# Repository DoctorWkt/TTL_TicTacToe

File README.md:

# TTL_TicTacToe

I've seen several circuits for two-player tic-tac-toe games on the Internet,
but I thought I'd try to design one with these constraints:

 + done with TTL components only, no CPU
 + minimum number of chips
 + not two player: human versus the board, board makes optimal moves

This is the repository for my result. The circuit uses flip-flops to
register both the human and the board's moves. The board has a register
which holds the current state of the board's moves. The board state and
the user's moves are combined to access a ROM to look up the next board move
and any tie or win result.
An [overview of the design](design_notes.md) is available. Here's
a [video](https://www.youtube.com/watch?v=WPPjL46z-Ag) of the board in action.

There are several versions of the design.

## Logisim Version

I built this [Logisim version](ttt_wkt.circ) in preparation for
designing the real circuit with TTL components. If you haven't used
[Logisim](http://www.cburch.com/logisim/) before, open up the _*.circ_
file. Now start the clock with a control-K (or use
_Simulate -> Ticks Enabled_). Now that the circuit is running, click on
the brown finger icon (the poke tool) at the top-left so that you can
press the game buttons.

Over on the right you will see a 3x3 grid. The white squares are the
pushbuttons to make a move. Next to each button is a red LED to register
the user's move and a blue LED for the board's moves.

Below this grid there is a Reset button and a "Who Goes First" button.
Press the "Who Goes First" button to toggle between the user moving
first and the board moving first. Then press the Reset button to clear
the board.

Now press the user moves buttons to make your moves. Immediately after
each move, the board will make a move. When a tie occurs, the Tie LED
will light up. When the board wins, the Win LED will light up.

Over on the left are the nine JK flip-flops to record the user's moves,
and the nine JK flip-flops to record the board's moves. Below that is
the ROM which generates a 4-bit value which is the new board's move.
The 4-bit board move goes into the 4:16 demultiplexer to generate the nine
lines which go to the nine JK flip-flops to record the board's moves.
Two of the 16 possible moves are used to indicate a tie or a board win.

The ROM also generates the next state of the board's moves. This is
recorded into a 4-bit register. See the [design notes](design_notes.md)
for details of the state number.

The circuit should come with the latest version of the ROM image. If you
ever regenerate the _ttt.rom_ file, here is how to load it into the circuit.
Right-click on the ROM device in the circuit and choose *Load image* and
choose the _ttl.rom_ file to load.

## Kicad Schematic

In the _Schematic/_ folder you will find a
[Kicad schematic](Schematic/schematic.pdf) for the circuit. This uses:

 + nine 74HC107 dual JK flip flops. Each one holds both the user and board
   move for one position on the board
 + one 28C256 32Kx8 EEPROM to look up the next board move. We only use
   8K of the space in the EEPROM.
 + one 74HC154 4:16 demultiplexer
 + one 75HC161 register to hold the board state number
 + one 555 to generate the clock signal
 + various LEDs to show the moves, and other sundry components.

I've also designed a [PCB](Figs/pcb2.jpg) to hold all the components.
The design has separate LEDs for user and board moves, but I've chosen to use
bi-colour LEDs so that there is a single physical LED for each board position:
green for the user, red for the board, off when empty.

## Generating the 28C256 EEPROM Contents

At the Linux command-line, run the command:

```
make
```

This will use the _gen_moves.pl_ script to generate the user-first moves file
_umoves_, and the board-first moves file _bmoves_. These are then parsed by
the _parse_moves.pl_ script to create the _ttt.rom_ file used by Logisim.

Finally, the _hex2bin_ script takes the _ttt.rom_ file, which is hex-encoded,
and converts it to the binary file _28C256.bin_ which can be burned to the
EEPROM.

If you have a MiniPro EEPROM burner and the _minipro_ command installed,

```
make write
```

will burn the _28C256.bin_ to a 28C256 chip with the MiniPro burner.

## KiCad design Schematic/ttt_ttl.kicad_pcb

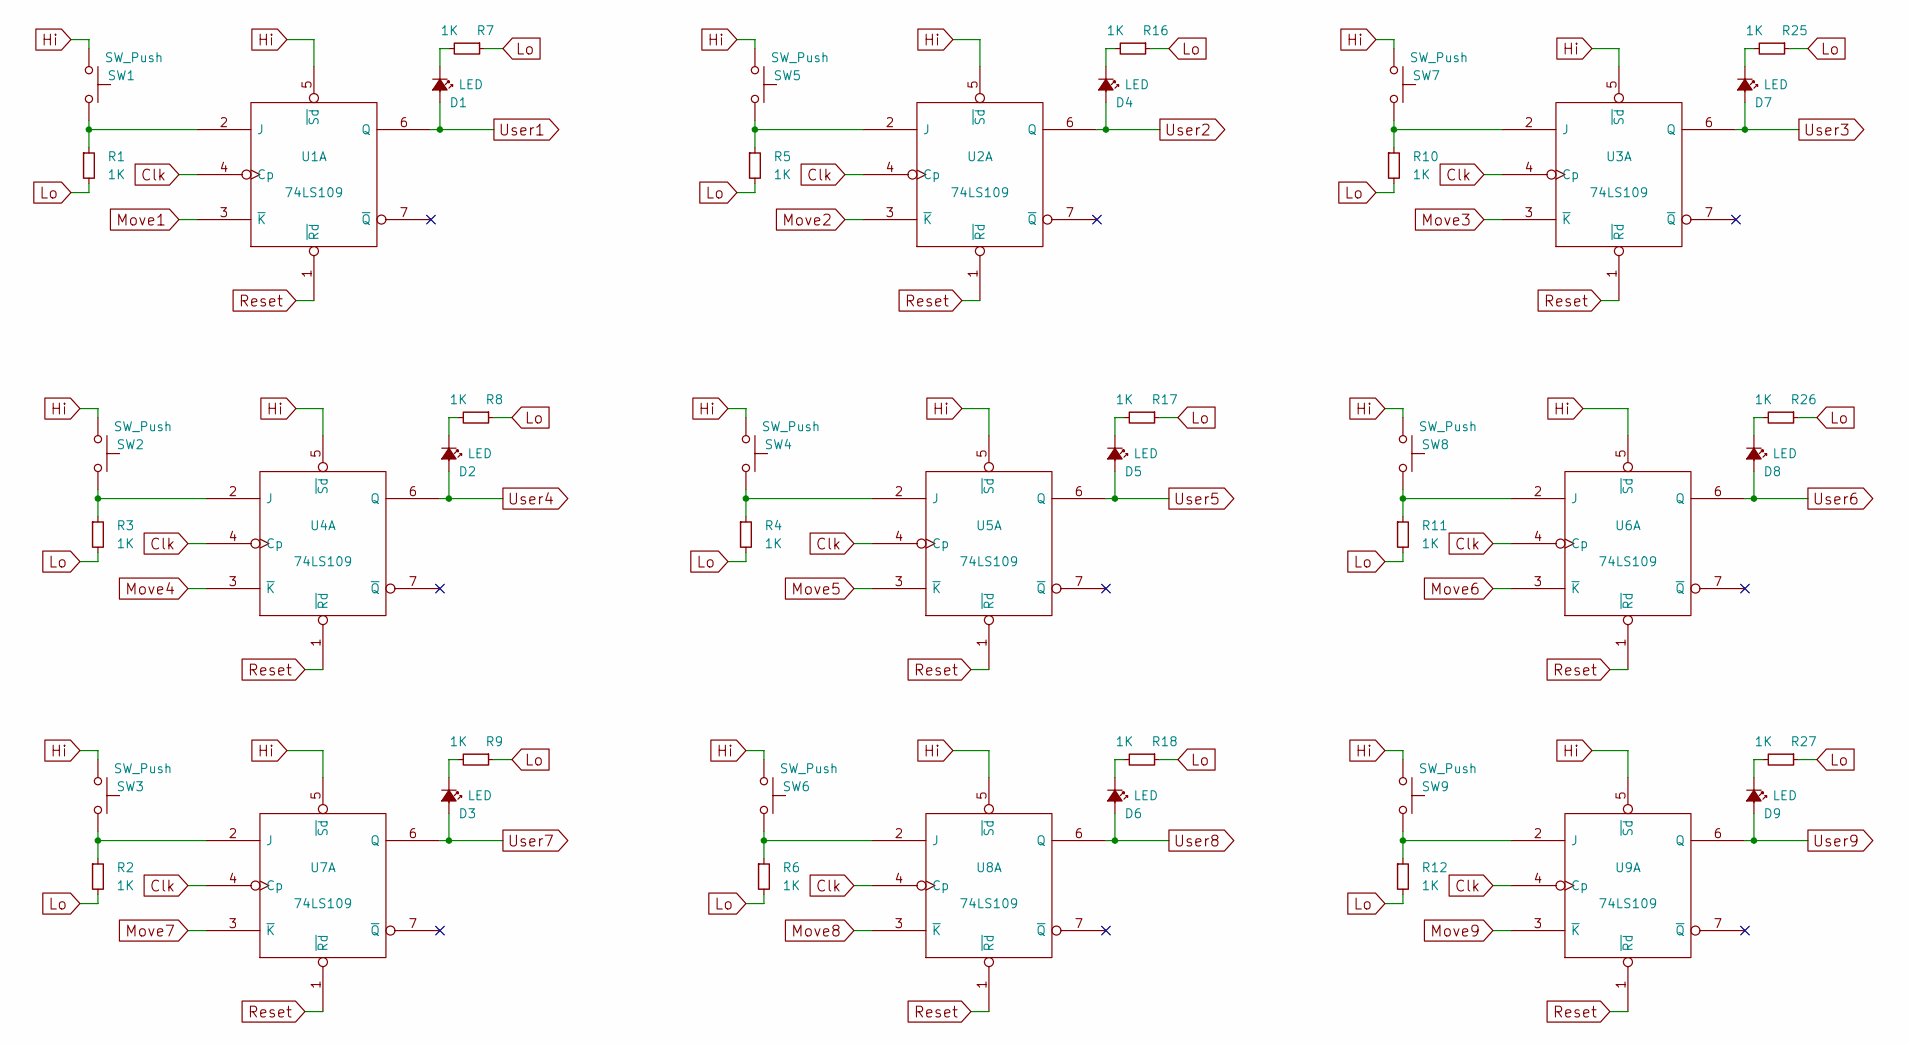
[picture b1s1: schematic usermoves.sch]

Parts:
D1, D2, D3, D4, D5, D6, D7, D8, D9: LED; LED_D3.0mm
R1, R2, R3, R4, R5, R6, R7, R8, R9, R10, R11, R12, R16, R17, R18, R25, R26, R27: 1K; R_Axial_DIN0207_L6.3mm_D2.5mm_P7.62mm_Horizontal
SW1, SW2, SW3, SW4, SW5, SW6, SW7, SW8, SW9: SW_Push; Push_E-Switch_KS01Q01
U1, U2, U3, U4, U5, U6, U7, U8, U9: 74LS109; DIP-16_W7.62mm

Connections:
Clk: U1.4 (Cp), U2.4 (Cp), U3.4 (Cp), U4.4 (Cp), U5.4 (Cp), U6.4 (Cp), U7.4 (Cp), U8.4 (Cp), U9.4 (Cp); also elsewhere on the board
Hi: SW1.1, SW2.1, SW3.1, SW4.1, SW5.1, SW6.1, SW7.1, SW8.1, SW9.1, U1.5 (~Sd), U1.16 (VCC), U2.5 (~Sd), U2.16 (VCC), U3.5 (~Sd), U3.16 (VCC), U4.5 (~Sd), U4.16 (VCC), U5.5 (~Sd), U5.16 (VCC), U6.5 (~Sd), U6.16 (VCC), U7.5 (~Sd), U7.16 (VCC), U8.5 (~Sd), U8.16 (VCC), U9.5 (~Sd), U9.16 (VCC); also elsewhere on the board
Lo: R1.2, R2.2, R3.2, R4.2, R5.2, R6.2, R7.1, R8.1, R9.1, R10.2, R11.2, R12.2, R16.1, R17.1, R18.1, R25.1, R26.1, R27.1, U1.8 (GND), U2.8 (GND), U3.8 (GND), U4.8 (GND), U5.8 (GND), U6.8 (GND), U7.8 (GND), U8.8 (GND), U9.8 (GND); also elsewhere on the board
Move1: U1.3 (~K); also elsewhere on the board
Move2: U2.3 (~K); also elsewhere on the board
Move3: U3.3 (~K); also elsewhere on the board
Move4: U4.3 (~K); also elsewhere on the board
Move5: U5.3 (~K); also elsewhere on the board
Move6: U6.3 (~K); also elsewhere on the board
Move7: U7.3 (~K); also elsewhere on the board
Move8: U8.3 (~K); also elsewhere on the board
Move9: U9.3 (~K); also elsewhere on the board
unnamed: D1.1 (K), R7.2
unnamed: D2.1 (K), R8.2
unnamed: D3.1 (K), R9.2
unnamed: D4.1 (K), R16.2
unnamed: D5.1 (K), R17.2
unnamed: D6.1 (K), R18.2
unnamed: D7.1 (K), R25.2
unnamed: D8.1 (K), R26.2
unnamed: D9.1 (K), R27.2
unnamed: R1.1, SW1.2, U1.2 (J)
unnamed: R2.1, SW3.2, U7.2 (J)
unnamed: R3.1, SW2.2, U4.2 (J)
unnamed: R4.1, SW4.2, U5.2 (J)
unnamed: R5.1, SW5.2, U2.2 (J)
unnamed: R6.1, SW6.2, U8.2 (J)
unnamed: R10.1, SW7.2, U3.2 (J)
unnamed: R11.1, SW8.2, U6.2 (J)
unnamed: R12.1, SW9.2, U9.2 (J)
Reset: U1.1 (~Rd), U2.1 (~Rd), U3.1 (~Rd), U4.1 (~Rd), U5.1 (~Rd), U6.1 (~Rd), U7.1 (~Rd), U8.1 (~Rd), U9.1 (~Rd); also elsewhere on the board
User1: D1.2 (A), U1.6 (Q); also elsewhere on the board
User2: D4.2 (A), U2.6 (Q); also elsewhere on the board
User3: D7.2 (A), U3.6 (Q); also elsewhere on the board
User4: D2.2 (A), U4.6 (Q); also elsewhere on the board
User5: D5.2 (A), U5.6 (Q); also elsewhere on the board
User6: D8.2 (A), U6.6 (Q); also elsewhere on the board
User7: D3.2 (A), U7.6 (Q); also elsewhere on the board
User8: D6.2 (A), U8.6 (Q); also elsewhere on the board
User9: D9.2 (A), U9.6 (Q); also elsewhere on the board

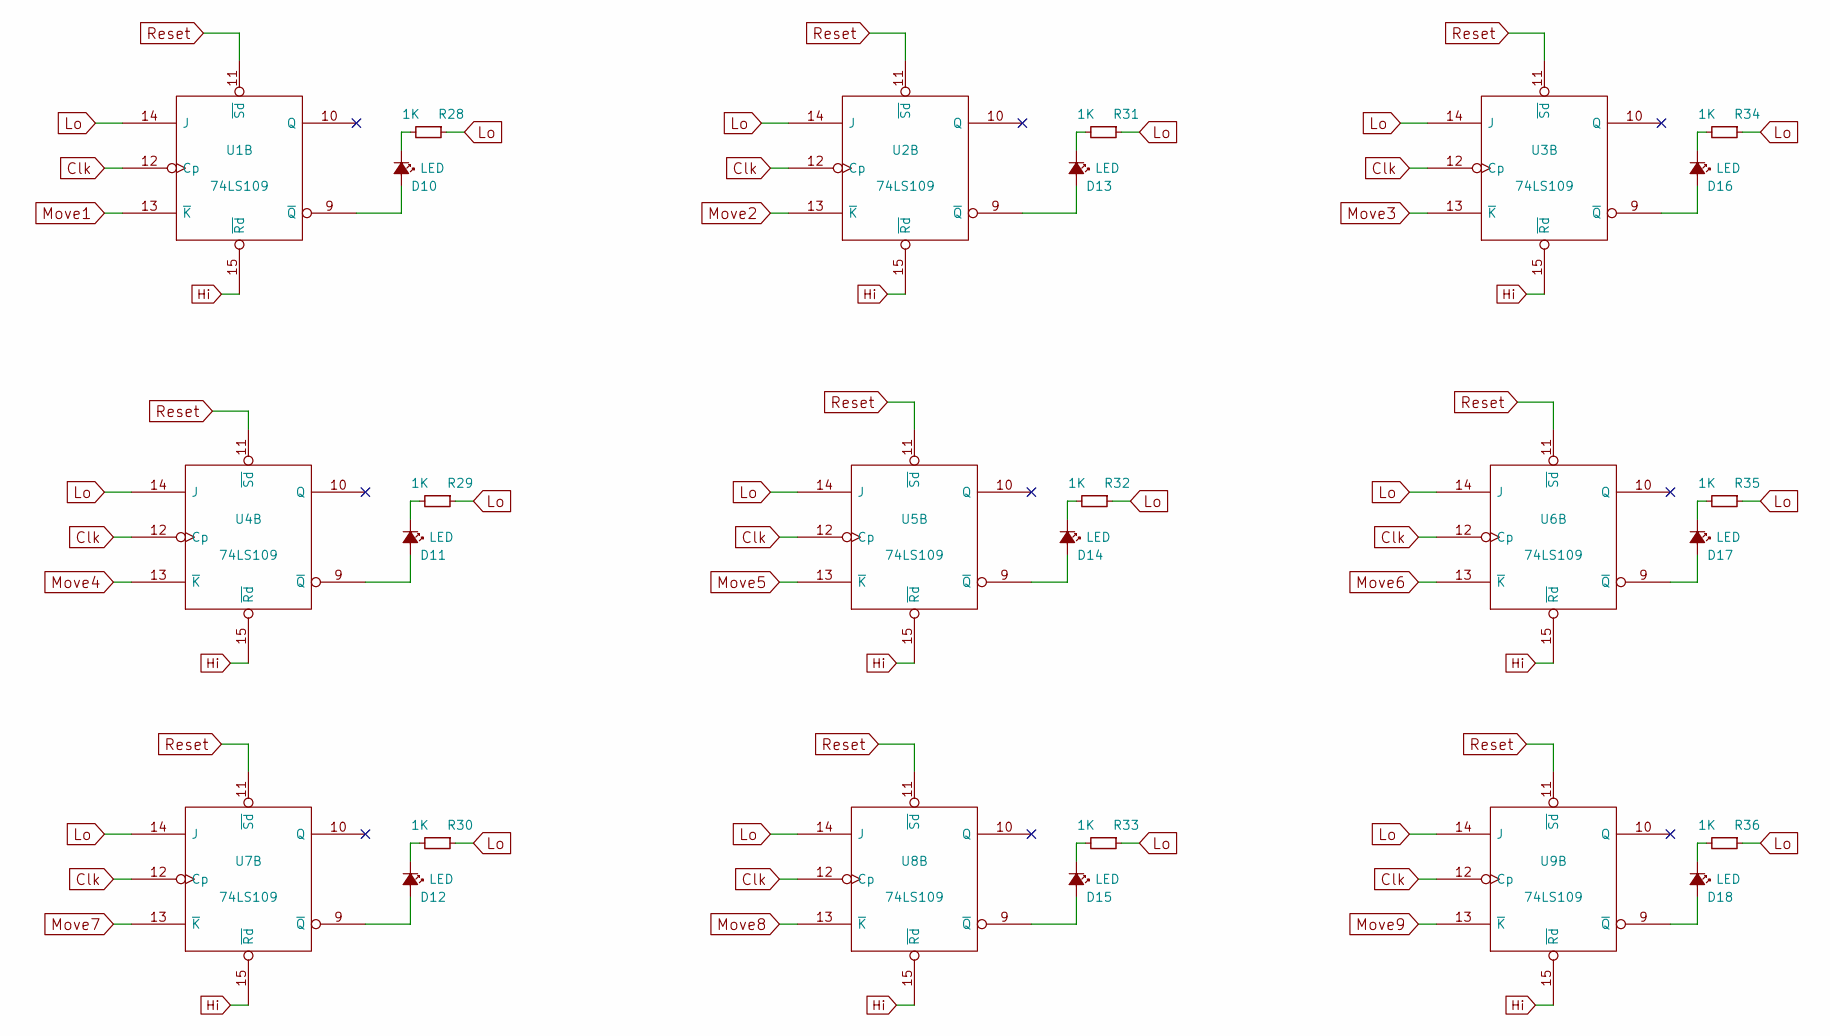
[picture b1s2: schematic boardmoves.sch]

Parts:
D10, D11, D12, D13, D14, D15, D16, D17, D18: LED; LED_D3.0mm
R28, R29, R30, R31, R32, R33, R34, R35, R36: 1K; R_Axial_DIN0207_L6.3mm_D2.5mm_P7.62mm_Horizontal
U1, U2, U3, U4, U5, U6, U7, U8, U9: 74LS109; DIP-16_W7.62mm

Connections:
Clk: U1.12 (Cp), U2.12 (Cp), U3.12 (Cp), U4.12 (Cp), U5.12 (Cp), U6.12 (Cp), U7.12 (Cp), U8.12 (Cp), U9.12 (Cp); also elsewhere on the board
Hi: U1.15 (~Rd), U1.16 (VCC), U2.15 (~Rd), U2.16 (VCC), U3.15 (~Rd), U3.16 (VCC), U4.15 (~Rd), U4.16 (VCC), U5.15 (~Rd), U5.16 (VCC), U6.15 (~Rd), U6.16 (VCC), U7.15 (~Rd), U7.16 (VCC), U8.15 (~Rd), U8.16 (VCC), U9.15 (~Rd), U9.16 (VCC); also elsewhere on the board
Lo: R28.1, R29.1, R30.1, R31.1, R32.1, R33.1, R34.1, R35.1, R36.1, U1.8 (GND), U1.14 (J), U2.8 (GND), U2.14 (J), U3.8 (GND), U3.14 (J), U4.8 (GND), U4.14 (J), U5.8 (GND), U5.14 (J), U6.8 (GND), U6.14 (J), U7.8 (GND), U7.14 (J), U8.8 (GND), U8.14 (J), U9.8 (GND), U9.14 (J); also elsewhere on the board
Move1: U1.13 (~K); also elsewhere on the board
Move2: U2.13 (~K); also elsewhere on the board
Move3: U3.13 (~K); also elsewhere on the board
Move4: U4.13 (~K); also elsewhere on the board
Move5: U5.13 (~K); also elsewhere on the board
Move6: U6.13 (~K); also elsewhere on the board
Move7: U7.13 (~K); also elsewhere on the board
Move8: U8.13 (~K); also elsewhere on the board
Move9: U9.13 (~K); also elsewhere on the board
unnamed: D10.1 (K), R28.2
unnamed: D10.2 (A), U1.9 (~Q)
unnamed: D11.1 (K), R29.2
unnamed: D11.2 (A), U4.9 (~Q)
unnamed: D12.1 (K), R30.2
unnamed: D12.2 (A), U7.9 (~Q)
unnamed: D13.1 (K), R31.2
unnamed: D13.2 (A), U2.9 (~Q)
unnamed: D14.1 (K), R32.2
unnamed: D14.2 (A), U5.9 (~Q)
unnamed: D15.1 (K), R33.2
unnamed: D15.2 (A), U8.9 (~Q)
unnamed: D16.1 (K), R34.2
unnamed: D16.2 (A), U3.9 (~Q)
unnamed: D17.1 (K), R35.2
unnamed: D17.2 (A), U6.9 (~Q)
unnamed: D18.1 (K), R36.2
unnamed: D18.2 (A), U9.9 (~Q)
Reset: U1.11 (~Sd), U2.11 (~Sd), U3.11 (~Sd), U4.11 (~Sd), U5.11 (~Sd), U6.11 (~Sd), U7.11 (~Sd), U8.11 (~Sd), U9.11 (~Sd); also elsewhere on the board

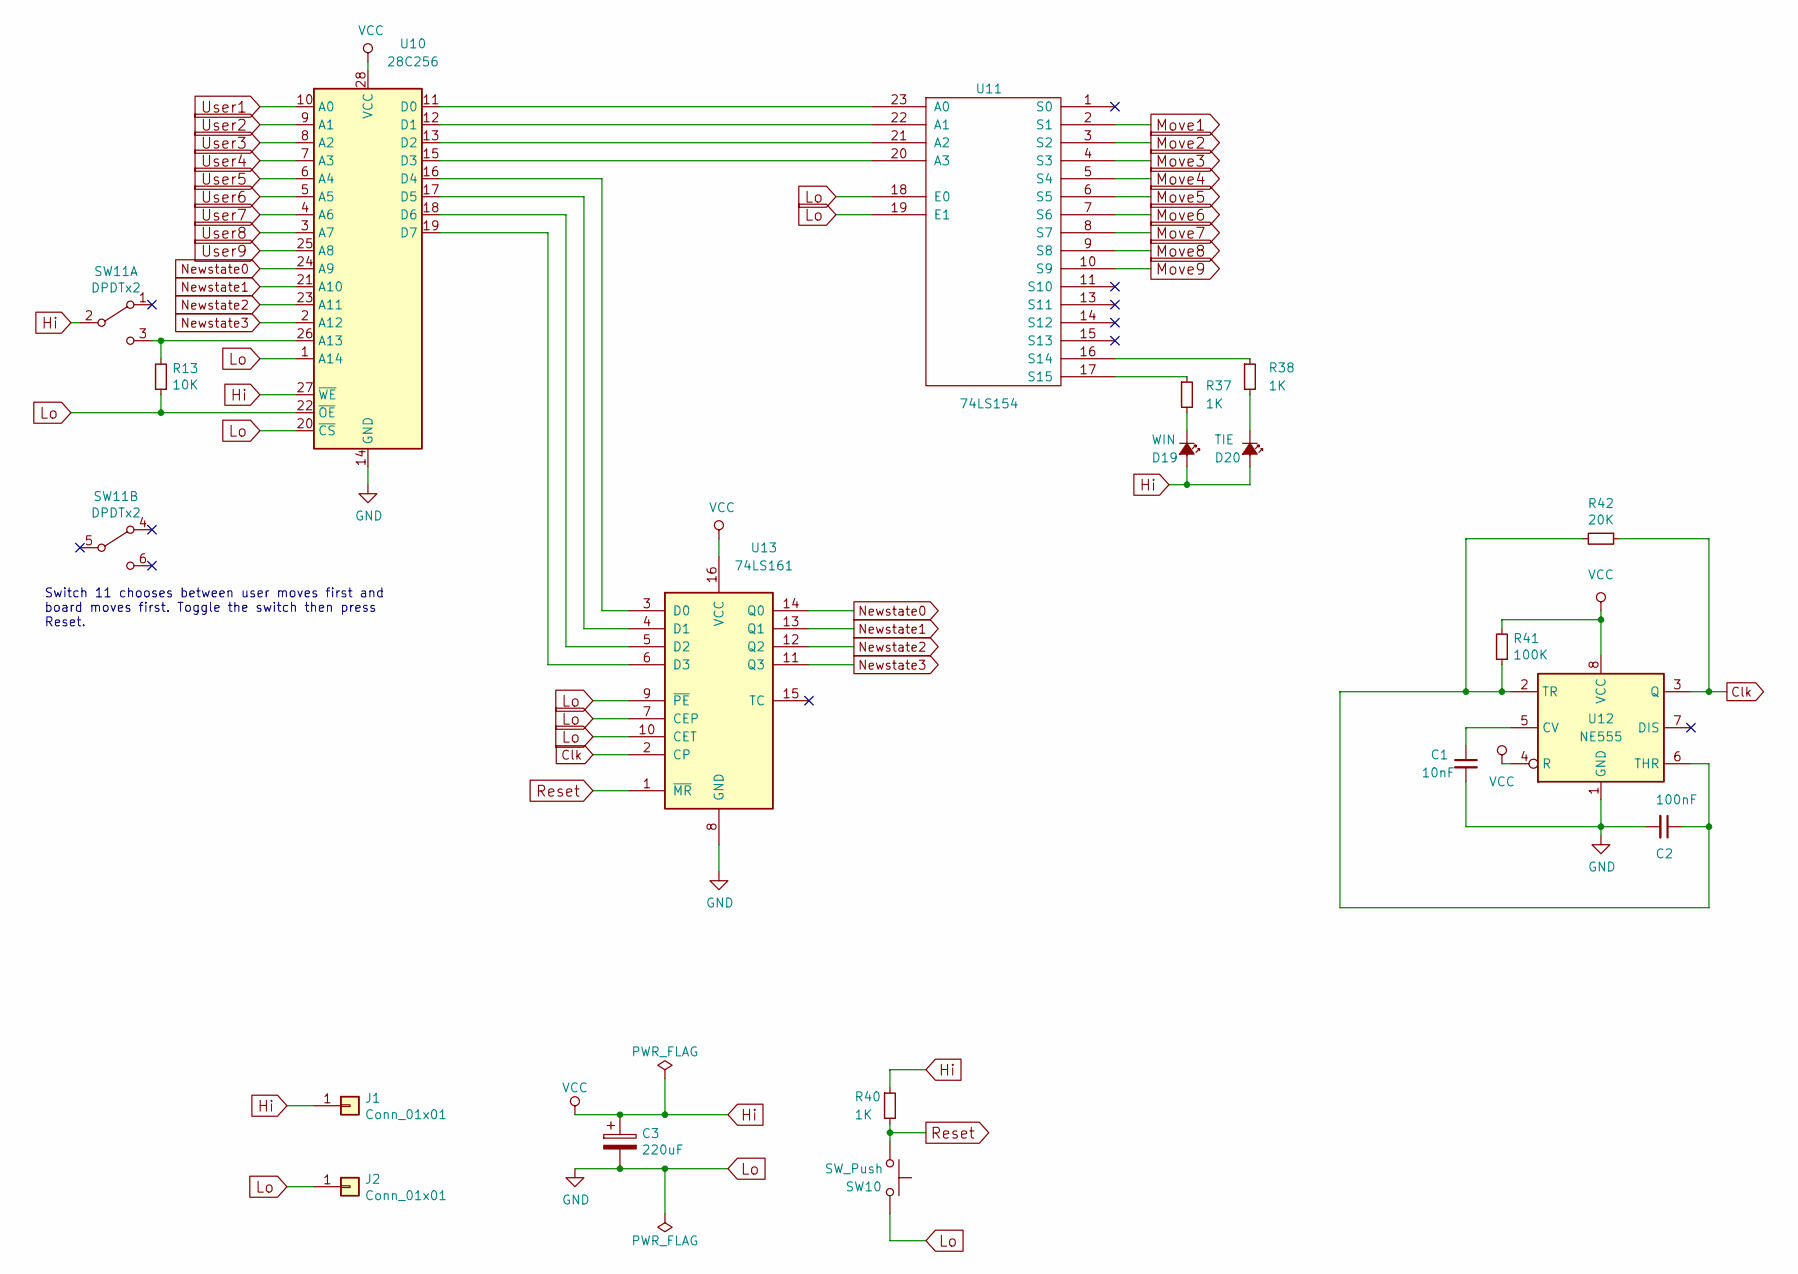
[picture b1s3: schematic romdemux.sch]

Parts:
C1: 10nF; C_Disc_D4.7mm_W2.5mm_P5.00mm
C2: 100nF; C_Disc_D4.7mm_W2.5mm_P5.00mm
C3: 220uF; CP_Radial_D10.0mm_P2.50mm
D19: WIN; LED_D3.0mm
D20: TIE; LED_D3.0mm
J1, J2: Conn_01x01; Pin_D1.0mm_L10.0mm
R13: 10K; R_Axial_DIN0207_L6.3mm_D2.5mm_P7.62mm_Horizontal
R37, R38, R40: 1K; R_Axial_DIN0207_L6.3mm_D2.5mm_P7.62mm_Horizontal
R41: 100K; R_Axial_DIN0207_L6.3mm_D2.5mm_P7.62mm_Horizontal
R42: 20K; R_Axial_DIN0207_L6.3mm_D2.5mm_P7.62mm_Horizontal
SW10: SW_Push; Push_E-Switch_KS01Q01
SW11: DPDTx2; DIP-6_W7.62mm
U10: 28C256; DIP-28_W15.24mm_Socket
U11: 74LS154; DIP-24_W7.62mm
U12: NE555; DIP-8_W7.62mm
U13: 74LS161; DIP-16_W7.62mm

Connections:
Clk: R42.1, U12.3 (Q), U13.2 (CP); also elsewhere on the board
Hi: C3.1, D19.2 (A), D20.2 (A), J1.1, R40.1, R41.2, SW11.2 (B), U10.27 (~WE), U10.28 (VCC), U11.24 (VCC), U12.4 (R), U12.8 (VCC), U13.16 (VCC); also elsewhere on the board
Lo: C1.2, C2.2, C3.2, J2.1, R13.1, SW10.2, U10.1 (A14), U10.14 (GND), U10.20 (~CS), U10.22 (~OE), U11.12 (GND), U11.18 (E0), U11.19 (E1), U12.1 (GND), U13.7 (CEP), U13.8 (GND), U13.9 (~PE), U13.10 (CET); also elsewhere on the board
Move1: U11.2 (S1); also elsewhere on the board
Move2: U11.3 (S2); also elsewhere on the board
Move3: U11.4 (S3); also elsewhere on the board
Move4: U11.5 (S4); also elsewhere on the board
Move5: U11.6 (S5); also elsewhere on the board
Move6: U11.7 (S6); also elsewhere on the board
Move7: U11.8 (S7); also elsewhere on the board
Move8: U11.9 (S8); also elsewhere on the board
Move9: U11.10 (S9); also elsewhere on the board
unnamed: C1.1, U12.5 (CV)
unnamed: C2.1, R41.1, R42.2, U12.2 (TR), U12.6 (THR)
unnamed: D19.1 (K), R37.2
unnamed: D20.1 (K), R38.2
unnamed: R13.2, SW11.3 (C), U10.26 (A13)
unnamed: R37.1, U11.17 (S15)
unnamed: R38.1, U11.16 (S14)
unnamed: U10.11 (D0), U11.23 (A0)
unnamed: U10.12 (D1), U11.22 (A1)
unnamed: U10.13 (D2), U11.21 (A2)
unnamed: U10.15 (D3), U11.20 (A3)
unnamed: U10.16 (D4), U13.3 (D0)
unnamed: U10.17 (D5), U13.4 (D1)
unnamed: U10.18 (D6), U13.5 (D2)
unnamed: U10.19 (D7), U13.6 (D3)
Newstate0: U10.24 (A9), U13.14 (Q0)
Newstate1: U10.21 (A10), U13.13 (Q1)
Newstate2: U10.23 (A11), U13.12 (Q2)
Newstate3: U10.2 (A12), U13.11 (Q3)
Reset: R40.2, SW10.1, U13.1 (~MR); also elsewhere on the board
User1: U10.10 (A0); also elsewhere on the board
User2: U10.9 (A1); also elsewhere on the board
User3: U10.8 (A2); also elsewhere on the board
User4: U10.7 (A3); also elsewhere on the board
User5: U10.6 (A4); also elsewhere on the board
User6: U10.5 (A5); also elsewhere on the board
User7: U10.4 (A6); also elsewhere on the board
User8: U10.3 (A7); also elsewhere on the board
User9: U10.25 (A8); also elsewhere on the board

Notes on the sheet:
Switch 11 chooses between user moves first and board moves first. Toggle the switch then press Reset.

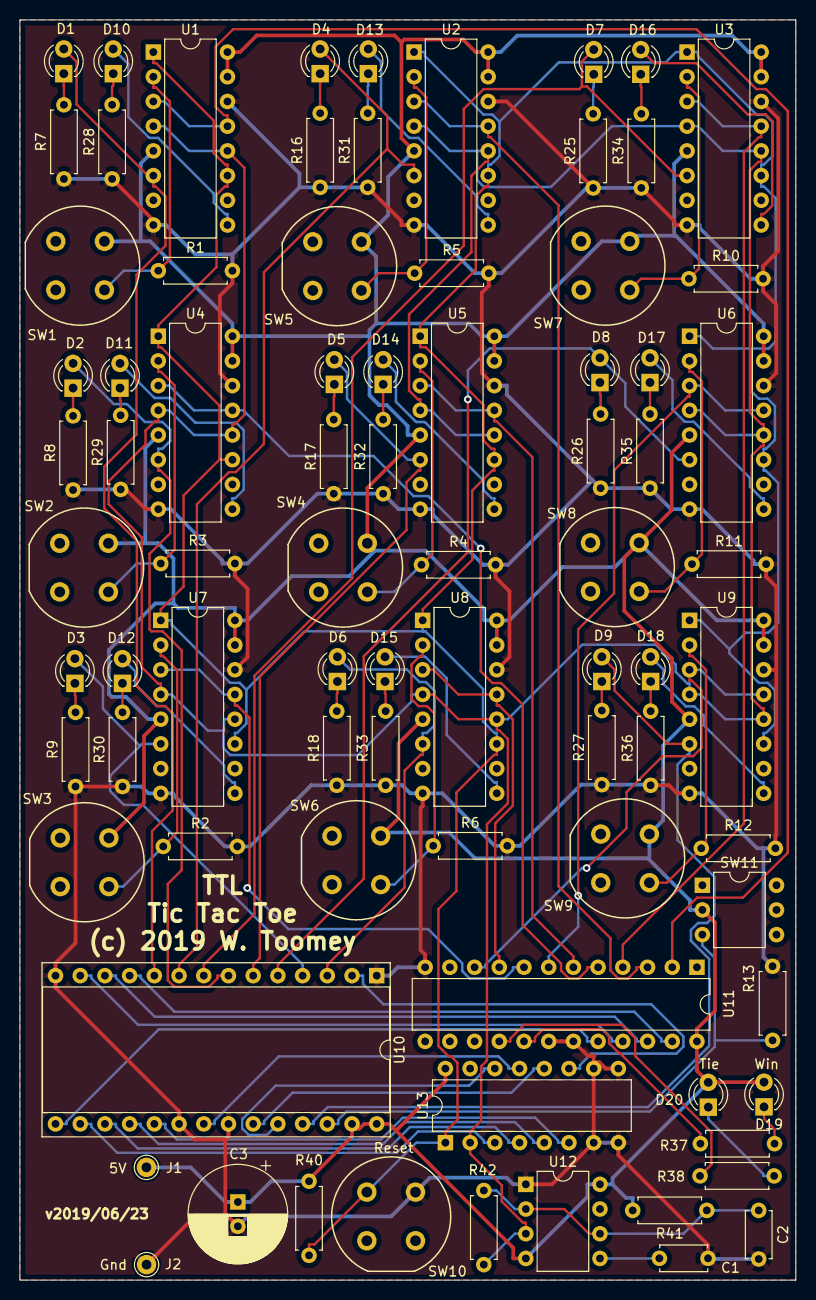
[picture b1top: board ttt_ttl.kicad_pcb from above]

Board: 2 copper layers, 79.8 x 129.5 mm, 82 parts (0 on the bottom side), 77 nets.

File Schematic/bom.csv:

Source:,/home/wkt/Schematic/ttt_ttl.sch,
Date:,Tue 18 Jun 2019 14:31:49 AEST,
Tool:,Eeschema 5.1.2-f72e74a~84~ubuntu18.04.1,
Component Count:,80,
Ref,Value,Footprint
C1,10nF,Capacitor_THT:C_Disc_D4.7mm_W2.5mm_P5.00mm
C2,100nF,Capacitor_THT:C_Disc_D4.7mm_W2.5mm_P5.00mm
C3,220uF,Capacitor_THT:CP_Radial_D10.0mm_P2.50mm
D1,LED,LED_THT:LED_D3.0mm
D2,LED,LED_THT:LED_D3.0mm
D3,LED,LED_THT:LED_D3.0mm
D4,LED,LED_THT:LED_D3.0mm
D5,LED,LED_THT:LED_D3.0mm
D6,LED,LED_THT:LED_D3.0mm
D7,LED,LED_THT:LED_D3.0mm
D8,LED,LED_THT:LED_D3.0mm
D9,LED,LED_THT:LED_D3.0mm
D10,LED,LED_THT:LED_D3.0mm
D11,LED,LED_THT:LED_D3.0mm
D12,LED,LED_THT:LED_D3.0mm
D13,LED,LED_THT:LED_D3.0mm
D14,LED,LED_THT:LED_D3.0mm
D15,LED,LED_THT:LED_D3.0mm
D16,LED,LED_THT:LED_D3.0mm
D17,LED,LED_THT:LED_D3.0mm
D18,LED,LED_THT:LED_D3.0mm
D19,WIN,LED_THT:LED_D3.0mm
D20,TIE,LED_THT:LED_D3.0mm
J1,Conn_01x01,Connector_Pin:Pin_D1.0mm_L10.0mm
J2,Conn_01x01,Connector_Pin:Pin_D1.0mm_L10.0mm
R1,1K,Resistor_THT:R_Axial_DIN0207_L6.3mm_D2.5mm_P7.62mm_Horizontal
R2,1K,Resistor_THT:R_Axial_DIN0207_L6.3mm_D2.5mm_P7.62mm_Horizontal
R3,1K,Resistor_THT:R_Axial_DIN0207_L6.3mm_D2.5mm_P7.62mm_Horizontal
R4,1K,Resistor_THT:R_Axial_DIN0207_L6.3mm_D2.5mm_P7.62mm_Horizontal
R5,1K,Resistor_THT:R_Axial_DIN0207_L6.3mm_D2.5mm_P7.62mm_Horizontal
R6,1K,Resistor_THT:R_Axial_DIN0207_L6.3mm_D2.5mm_P7.62mm_Horizontal
R7,1K,Resistor_THT:R_Axial_DIN0207_L6.3mm_D2.5mm_P7.62mm_Horizontal
R8,1K,Resistor_THT:R_Axial_DIN0207_L6.3mm_D2.5mm_P7.62mm_Horizontal
R9,1K,Resistor_THT:R_Axial_DIN0207_L6.3mm_D2.5mm_P7.62mm_Horizontal
R10,1K,Resistor_THT:R_Axial_DIN0207_L6.3mm_D2.5mm_P7.62mm_Horizontal
R11,1K,Resistor_THT:R_Axial_DIN0207_L6.3mm_D2.5mm_P7.62mm_Horizontal
R12,1K,Resistor_THT:R_Axial_DIN0207_L6.3mm_D2.5mm_P7.62mm_Horizontal
R16,1K,Resistor_THT:R_Axial_DIN0207_L6.3mm_D2.5mm_P7.62mm_Horizontal
R17,1K,Resistor_THT:R_Axial_DIN0207_L6.3mm_D2.5mm_P7.62mm_Horizontal
R18,1K,Resistor_THT:R_Axial_DIN0207_L6.3mm_D2.5mm_P7.62mm_Horizontal
R25,1K,Resistor_THT:R_Axial_DIN0207_L6.3mm_D2.5mm_P7.62mm_Horizontal
R26,1K,Resistor_THT:R_Axial_DIN0207_L6.3mm_D2.5mm_P7.62mm_Horizontal
R27,1K,Resistor_THT:R_Axial_DIN0207_L6.3mm_D2.5mm_P7.62mm_Horizontal
R28,1K,Resistor_THT:R_Axial_DIN0207_L6.3mm_D2.5mm_P7.62mm_Horizontal
R29,1K,Resistor_THT:R_Axial_DIN0207_L6.3mm_D2.5mm_P7.62mm_Horizontal
R30,1K,Resistor_THT:R_Axial_DIN0207_L6.3mm_D2.5mm_P7.62mm_Horizontal
R31,1K,Resistor_THT:R_Axial_DIN0207_L6.3mm_D2.5mm_P7.62mm_Horizontal
R32,1K,Resistor_THT:R_Axial_DIN0207_L6.3mm_D2.5mm_P7.62mm_Horizontal
R33,1K,Resistor_THT:R_Axial_DIN0207_L6.3mm_D2.5mm_P7.62mm_Horizontal
R34,1K,Resistor_THT:R_Axial_DIN0207_L6.3mm_D2.5mm_P7.62mm_Horizontal
R35,1K,Resistor_THT:R_Axial_DIN0207_L6.3mm_D2.5mm_P7.62mm_Horizontal
R36,1K,Resistor_THT:R_Axial_DIN0207_L6.3mm_D2.5mm_P7.62mm_Horizontal
R37,1K,Resistor_THT:R_Axial_DIN0207_L6.3mm_D2.5mm_P7.62mm_Horizontal
R38,1K,Resistor_THT:R_Axial_DIN0207_L6.3mm_D2.5mm_P7.62mm_Horizontal
R40,1K,Resistor_THT:R_Axial_DIN0207_L6.3mm_D2.5mm_P7.62mm_Horizontal
R41,100K,Resistor_THT:R_Axial_DIN0207_L6.3mm_D2.5mm_P7.62mm_Horizontal
R42,20K,Resistor_THT:R_Axial_DIN0207_L6.3mm_D2.5mm_P7.62mm_Horizontal
SW1,SW_Push,Button_Switch_THT:Push_E-Switch_KS01Q01
SW2,SW_Push,Button_Switch_THT:Push_E-Switch_KS01Q01
SW3,SW_Push,Button_Switch_THT:Push_E-Switch_KS01Q01
SW4,SW_Push,Button_Switch_THT:Push_E-Switch_KS01Q01
SW5,SW_Push,Button_Switch_THT:Push_E-Switch_KS01Q01
SW6,SW_Push,Button_Switch_THT:Push_E-Switch_KS01Q01
SW7,SW_Push,Button_Switch_THT:Push_E-Switch_KS01Q01
SW8,SW_Push,Button_Switch_THT:Push_E-Switch_KS01Q01
SW9,SW_Push,Button_Switch_THT:Push_E-Switch_KS01Q01
SW10,SW_Push,Button_Switch_THT:Push_E-Switch_KS01Q01
SW11,SW_DPDTx2,Package_DIP:DIP-6_W7.62mm,TL2230EEF140
U1,74HC109,Package_DIP:DIP-16_W7.62mm
U2,74HC109,Package_DIP:DIP-16_W7.62mm
U3,74HC109,Package_DIP:DIP-16_W7.62mm
U4,74HC109,Package_DIP:DIP-16_W7.62mm
U5,74HC109,Package_DIP:DIP-16_W7.62mm
U6,74HC109,Package_DIP:DIP-16_W7.62mm
U7,74HC109,Package_DIP:DIP-16_W7.62mm
U8,74HC109,Package_DIP:DIP-16_W7.62mm
U9,74HC109,Package_DIP:DIP-16_W7.62mm
U10,28C256,Package_DIP:DIP-28_W15.24mm_Socket
U11,74HC154,Package_DIP:DIP-24_W7.62mm
U12,NE555,Package_DIP:DIP-8_W7.62mm
U13,74HC161,Package_DIP:DIP-16_W7.62mm

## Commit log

2019-06-05 Added the Logisim circuit and the working ROM image for it
2019-06-05 More details of the circuit.
2019-06-05 More instructions for README.
2019-06-05 More README
2019-06-05 Added some design notes
2019-06-05 I've made a start on an actual circuit and PCB for the game.
2019-06-06 More work on the circuit and the PCB layout.
2019-06-11 I gave up on trying to use a smaller ROM.
    I've moved the LEDs in the Logisim version to a 3x3 grid in the
    top-right corner of the circuit.
2019-06-11 Added a BoM and a PDF schematic
2019-06-11 Fixed up the reset line circuitry
2019-06-11 Journal update: breadboard is started
2019-06-12 Updated the schematic and PCB with the new flip-flip pinouts and footprints.
2019-06-12 Updated the schematic PDF and the Readme.
2019-06-12 Small typo in README.md.
2019-06-12 Updated the bill of materials.
2019-06-12 Another BOM fix
2019-06-12 Added a PCB image and moved all images to Figs/
2019-06-12 Fixed ROM part, was 27C020, should be 27C2001
2019-06-13 I've started on work to use a smaller ROM, but not fully working yet.
2019-06-13 Indicate which last version was working.
2019-06-13 Argh, typo!
2019-06-16 Smaller 8Kx8 EEPROM is working
    I managed to get the code to generate a ROM file which uses a 4-bit board
    state plus the user's moves to look up the net board move and the next
    board state. I've redone the schematic, PCB and I've started on the
    documentation. I need to redraw the design diagram.
2019-06-16 I improved the design notes and figures.
2019-06-17 I bought different pushbuttons, so I updated the PCB design.
2019-06-17 Added links to the design notes in the README.md
2019-06-17 Improved the design notes a bit more
2019-06-18 Small circuit change. Tie/win LEDs must connect to demux active low output.
2019-06-18 Changed to horizontal resistors on PCB.
    This resulted in only two vias, so that's nice.
2019-06-18 Updated the PCB image
2019-06-19 Did some more breadboard wiring, updated the journal.
2019-06-20 Edging closer to a full circuit on the breadboard.
2019-06-20 I've played the first games on the breadboard version.
2019-06-20 Fixed a wiring issue and the breadboard version works perfectly!
2019-06-23 Thanks to Ken Yap, I modified the project to optionally allow the board to move first.
2019-06-23 Updated the PCB version number.
2019-06-23 play_usingrom.pl is no longer needed.
2019-06-23 Updated the PDF of the schematic.
2019-06-27 Another journal entry.
2019-06-27 Tidied up journal entry.
2019-06-27 Arg typos!
2019-06-28 My final journal entry with a PCB photo.
2019-06-28 Added links to the Youtube video.
2019-06-28 Changed PCB link to real photo.

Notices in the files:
Schematic/ttt_ttl.kicad_pcb:
(c) 2019 W. Toomey
